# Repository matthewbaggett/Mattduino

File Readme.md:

# Mattduino Arduino Mega clone

## Why? 
Because I wanted to convert the minimal circuit of an Arduino Mega into a Eaglecad Design Block. And now that I've done that, I should make it into a schematic with all the pins broken out and aligned just like a real Arduino Mega.

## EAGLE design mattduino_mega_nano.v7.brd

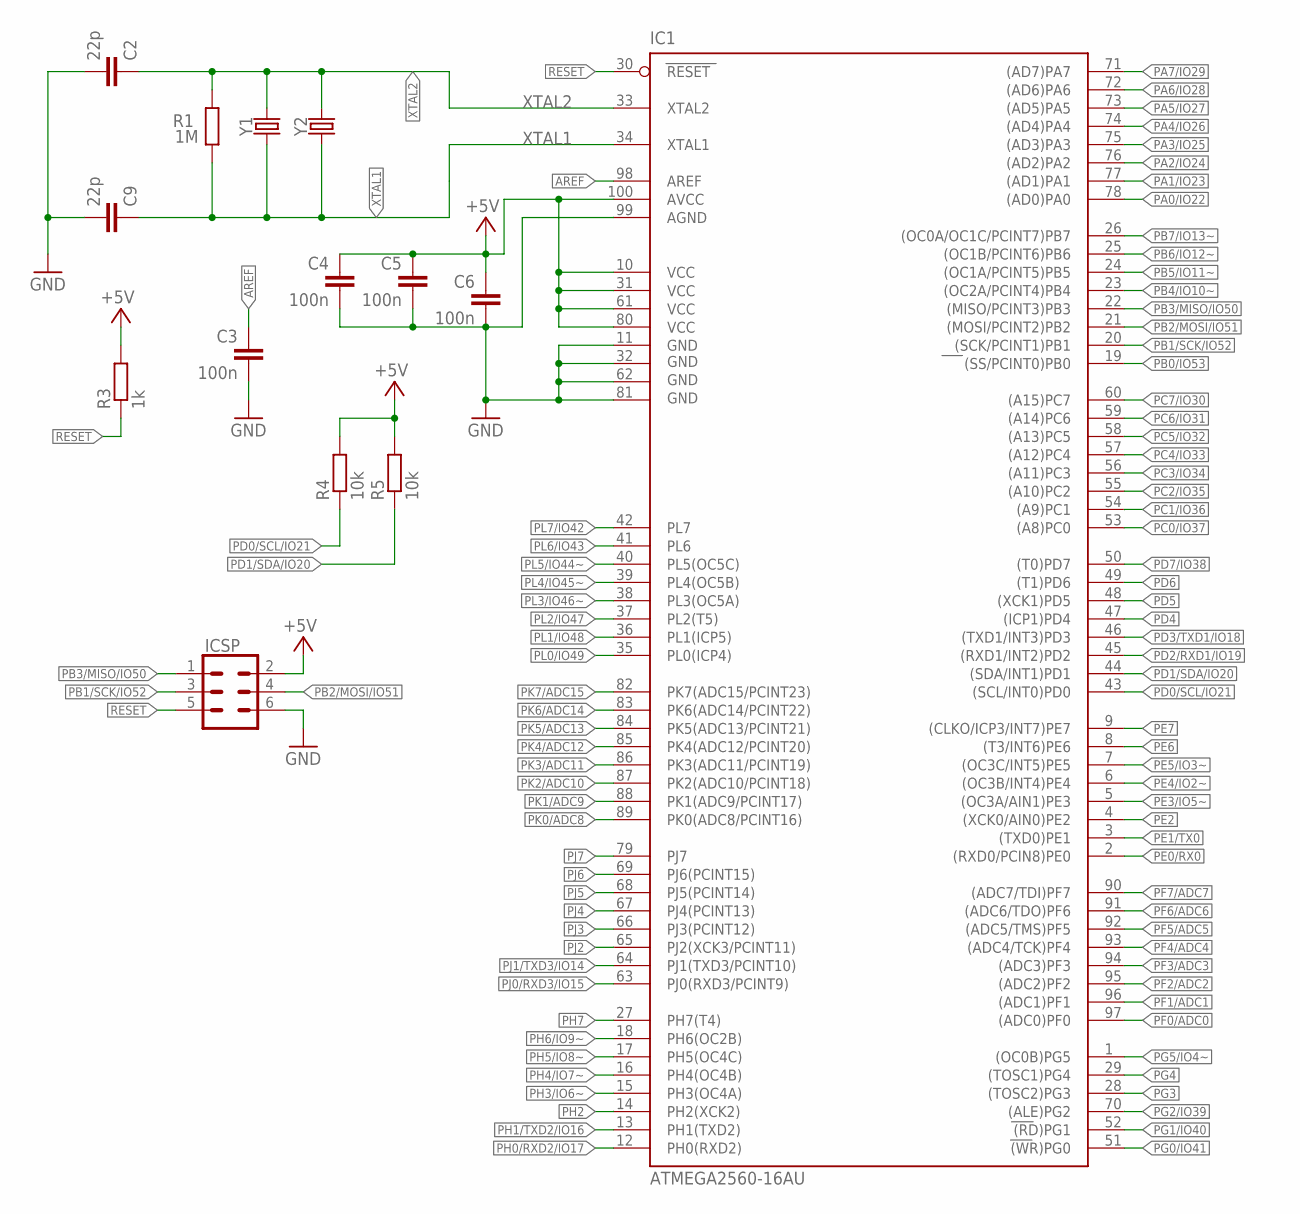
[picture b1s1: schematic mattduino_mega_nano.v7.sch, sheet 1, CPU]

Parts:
C2, C9: 22p; C0603
C3, C4, C5, C6: 100n; C0603
IC1: ATMEGA2560-16AU; TQFP100
ICSP: CONN_03X2SHROUD; 2X3-SHROUDED
R1: 1M; R0603
R3: 1k; R0603
R4, R5: 10k; R0603
Y1: CRYSTALPTH-HC49UV; HC49U
Y2: CRYSTALSMD-HC49UP; HC49UP

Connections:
+5V: C4.1, C5.1, C6.1, IC1.10 (VCC), IC1.31 (VCC1), IC1.61 (VCC2), IC1.80 (VCC3), IC1.100 (AVCC), ICSP.2, R3.2, R4.2, R5.2; also elsewhere on the board
AREF: C3.1, IC1.98 (AREF)
GND: C2.2, C3.2, C4.2, C5.2, C6.2, C9.2, IC1.11 (GND), IC1.32 (GND1), IC1.62 (GND2), IC1.81 (GND3), IC1.99 (AGND), ICSP.6; also elsewhere on the board
PA0/IO22: IC1.78 ((AD0)PA0); also elsewhere on the board
PA1/IO23: IC1.77 ((AD1)PA1); also elsewhere on the board
PA2/IO24: IC1.76 ((AD2)PA2); also elsewhere on the board
PA3/IO25: IC1.75 ((AD3)PA3); also elsewhere on the board
PA4/IO26: IC1.74 ((AD4)PA4); also elsewhere on the board
PA5/IO27: IC1.73 ((AD5)PA5); also elsewhere on the board
PA6/IO28: IC1.72 ((AD6)PA6); also elsewhere on the board
PA7/IO29: IC1.71 ((AD7)PA7); also elsewhere on the board
PB0/IO53: IC1.19 ((SS/PCINT0)PB0); also elsewhere on the board
PB1/SCK/IO52: IC1.20 ((SCK/PCINT1)PB1), ICSP.3; also elsewhere on the board
PB2/MOSI/IO51: IC1.21 ((MOSI/PCINT2)PB2), ICSP.4; also elsewhere on the board
PB3/MISO/IO50: IC1.22 ((MISO/PCINT3)PB3), ICSP.1; also elsewhere on the board
PB4/IO10~: IC1.23 ((OC2A/PCINT4)PB4); also elsewhere on the board
PB5/IO11~: IC1.24 ((OC1A/PCINT5)PB5); also elsewhere on the board
PB6/IO12~: IC1.25 ((OC1B/PCINT6)PB6); also elsewhere on the board
PB7/IO13~: IC1.26 ((OC0A/OC1C/PCINT7)PB7); also elsewhere on the board
PC0/IO37: IC1.53 ((A8)PC0); also elsewhere on the board
PC1/IO36: IC1.54 ((A9)PC1); also elsewhere on the board
PC2/IO35: IC1.55 ((A10)PC2); also elsewhere on the board
PC3/IO34: IC1.56 ((A11)PC3); also elsewhere on the board
PC4/IO33: IC1.57 ((A12)PC4); also elsewhere on the board
PC5/IO32: IC1.58 ((A13)PC5); also elsewhere on the board
PC6/IO31: IC1.59 ((A14)PC6); also elsewhere on the board
PC7/IO30: IC1.60 ((A15)PC7); also elsewhere on the board
PD0/SCL/IO21: IC1.43 ((SCL/INT0)PD0), R4.1; also elsewhere on the board
PD1/SDA/IO20: IC1.44 ((SDA/INT1)PD1), R5.1; also elsewhere on the board
PD2/RXD1/IO19: IC1.45 ((RXD1/INT2)PD2); also elsewhere on the board
PD3/TXD1/IO18: IC1.46 ((TXD1/INT3)PD3); also elsewhere on the board
PD4: IC1.47 ((ICP1)PD4)
PD5: IC1.48 ((XCK1)PD5)
PD6: IC1.49 ((T1)PD6)
PD7/IO38: IC1.50 ((T0)PD7); also elsewhere on the board
PE0/RX0: IC1.2 ((RXD0/PCIN8)PE0); also elsewhere on the board
PE1/TX0: IC1.3 ((TXD0)PE1); also elsewhere on the board
PE2: IC1.4 ((XCK0/AIN0)PE2)
PE3/IO5~: IC1.5 ((OC3A/AIN1)PE3); also elsewhere on the board
PE4/IO2~: IC1.6 ((OC3B/INT4)PE4); also elsewhere on the board
PE5/IO3~: IC1.7 ((OC3C/INT5)PE5); also elsewhere on the board
PE6: IC1.8 ((T3/INT6)PE6); also elsewhere on the board
PE7: IC1.9 ((CLKO/ICP3/INT7)PE7); also elsewhere on the board
PF0/ADC0: IC1.97 ((ADC0)PF0); also elsewhere on the board
PF1/ADC1: IC1.96 ((ADC1)PF1); also elsewhere on the board
PF2/ADC2: IC1.95 ((ADC2)PF2); also elsewhere on the board
PF3/ADC3: IC1.94 ((ADC3)PF3); also elsewhere on the board
PF4/ADC4: IC1.93 ((ADC4/TCK)PF4); also elsewhere on the board
PF5/ADC5: IC1.92 ((ADC5/TMS)PF5); also elsewhere on the board
PF6/ADC6: IC1.91 ((ADC6/TDO)PF6); also elsewhere on the board
PF7/ADC7: IC1.90 ((ADC7/TDI)PF7); also elsewhere on the board
PG0/IO41: IC1.51 ((WR)PG0); also elsewhere on the board
PG1/IO40: IC1.52 ((RD)PG1); also elsewhere on the board
PG2/IO39: IC1.70 ((ALE)PG2); also elsewhere on the board
PG3: IC1.28 ((TOSC2)PG3)
PG4: IC1.29 ((TOSC1)PG4)
PG5/IO4~: IC1.1 ((OC0B)PG5); also elsewhere on the board
PH0/RXD2/IO17: IC1.12 (PH0(RXD2)); also elsewhere on the board
PH1/TXD2/IO16: IC1.13 (PH1(TXD2)); also elsewhere on the board
PH2: IC1.14 (PH2(XCK2)); also elsewhere on the board
PH3/IO6~: IC1.15 (PH3(OC4A)); also elsewhere on the board
PH4/IO7~: IC1.16 (PH4(OC4B)); also elsewhere on the board
PH5/IO8~: IC1.17 (PH5(OC4C)); also elsewhere on the board
PH6/IO9~: IC1.18 (PH6(OC2B)); also elsewhere on the board
PH7: IC1.27 (PH7(T4))
PJ0/RXD3/IO15: IC1.63 (PJ0(RXD3/PCINT9)); also elsewhere on the board
PJ1/TXD3/IO14: IC1.64 (PJ1(TXD3/PCINT10)); also elsewhere on the board
PJ2: IC1.65 (PJ2(XCK3/PCINT11))
PJ3: IC1.66 (PJ3(PCINT12))
PJ4: IC1.67 (PJ4(PCINT13))
PJ5: IC1.68 (PJ5(PCINT14))
PJ6: IC1.69 (PJ6(PCINT15))
PJ7: IC1.79 (PJ7)
PK0/ADC8: IC1.89 (PK0(ADC8/PCINT16)); also elsewhere on the board
PK1/ADC9: IC1.88 (PK1(ADC9/PCINT17)); also elsewhere on the board
PK2/ADC10: IC1.87 (PK2(ADC10/PCINT18)); also elsewhere on the board
PK3/ADC11: IC1.86 (PK3(ADC11/PCINT19)); also elsewhere on the board
PK4/ADC12: IC1.85 (PK4(ADC12/PCINT20)); also elsewhere on the board
PK5/ADC13: IC1.84 (PK5(ADC13/PCINT21)); also elsewhere on the board
PK6/ADC14: IC1.83 (PK6(ADC14/PCINT22)); also elsewhere on the board
PK7/ADC15: IC1.82 (PK7(ADC15/PCINT23)); also elsewhere on the board
PL0/IO49: IC1.35 (PL0(ICP4)); also elsewhere on the board
PL1/IO48: IC1.36 (PL1(ICP5)); also elsewhere on the board
PL2/IO47: IC1.37 (PL2(T5)); also elsewhere on the board
PL3/IO46~: IC1.38 (PL3(OC5A)); also elsewhere on the board
PL4/IO45~: IC1.39 (PL4(OC5B)); also elsewhere on the board
PL5/IO44~: IC1.40 (PL5(OC5C)); also elsewhere on the board
PL6/IO43: IC1.41 (PL6); also elsewhere on the board
PL7/IO42: IC1.42 (PL7); also elsewhere on the board
RESET: IC1.30 (RESET), ICSP.5, R3.1; also elsewhere on the board
XTAL1: C9.1, IC1.34 (XTAL1), R1.1, Y1.1, Y2.1
XTAL2: C2.1, IC1.33 (XTAL2), R1.2, Y1.2, Y2.2

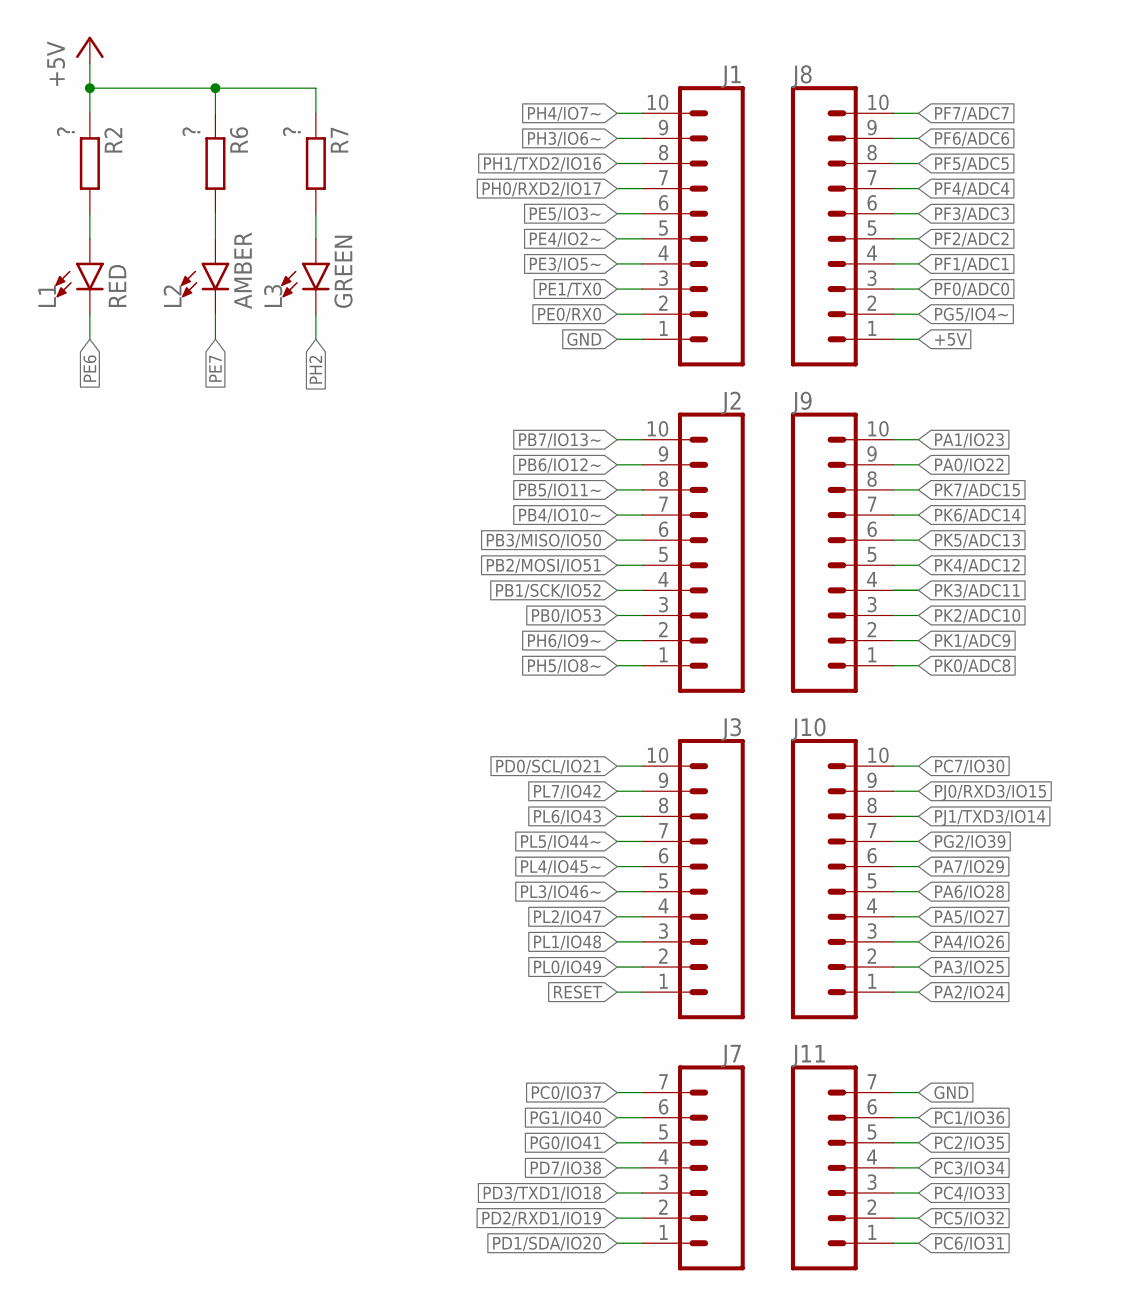
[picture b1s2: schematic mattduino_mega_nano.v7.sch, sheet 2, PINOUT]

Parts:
J1, J2, J3, J8, J9, J10: CONN_10LOCK; 1X10_LOCK
J7, J11: CONN_07LOCK; 1X07_LOCK
L1: RED; LED-0603
L2: AMBER; LED-0603
L3: GREEN; LED-0603
R2, R6, R7: ?; R0603

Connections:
+5V: J8.1, R2.1, R6.1, R7.1; also elsewhere on the board
GND: J1.1, J11.7; also elsewhere on the board
unnamed: L1.A, R2.2
unnamed: L2.A, R6.2
unnamed: L3.A, R7.2
PA0/IO22: J9.9; also elsewhere on the board
PA1/IO23: J9.10; also elsewhere on the board
PA2/IO24: J10.1; also elsewhere on the board
PA3/IO25: J10.2; also elsewhere on the board
PA4/IO26: J10.3; also elsewhere on the board
PA5/IO27: J10.4; also elsewhere on the board
PA6/IO28: J10.5; also elsewhere on the board
PA7/IO29: J10.6; also elsewhere on the board
PB0/IO53: J2.3; also elsewhere on the board
PB1/SCK/IO52: J2.4; also elsewhere on the board
PB2/MOSI/IO51: J2.5; also elsewhere on the board
PB3/MISO/IO50: J2.6; also elsewhere on the board
PB4/IO10~: J2.7; also elsewhere on the board
PB5/IO11~: J2.8; also elsewhere on the board
PB6/IO12~: J2.9; also elsewhere on the board
PB7/IO13~: J2.10; also elsewhere on the board
PC0/IO37: J7.7; also elsewhere on the board
PC1/IO36: J11.6; also elsewhere on the board
PC2/IO35: J11.5; also elsewhere on the board
PC3/IO34: J11.4; also elsewhere on the board
PC4/IO33: J11.3; also elsewhere on the board
PC5/IO32: J11.2; also elsewhere on the board
PC6/IO31: J11.1; also elsewhere on the board
PC7/IO30: J10.10; also elsewhere on the board
PD0/SCL/IO21: J3.10; also elsewhere on the board
PD1/SDA/IO20: J7.1; also elsewhere on the board
PD2/RXD1/IO19: J7.2; also elsewhere on the board
PD3/TXD1/IO18: J7.3; also elsewhere on the board
PD7/IO38: J7.4; also elsewhere on the board
PE0/RX0: J1.2; also elsewhere on the board
PE1/TX0: J1.3; also elsewhere on the board
PE3/IO5~: J1.4; also elsewhere on the board
PE4/IO2~: J1.5; also elsewhere on the board
PE5/IO3~: J1.6; also elsewhere on the board
PE6: L1.C; also elsewhere on the board
PE7: L2.C; also elsewhere on the board
PF0/ADC0: J8.3; also elsewhere on the board
PF1/ADC1: J8.4; also elsewhere on the board
PF2/ADC2: J8.5; also elsewhere on the board
PF3/ADC3: J8.6; also elsewhere on the board
PF4/ADC4: J8.7; also elsewhere on the board
PF5/ADC5: J8.8; also elsewhere on the board
PF6/ADC6: J8.9; also elsewhere on the board
PF7/ADC7: J8.10; also elsewhere on the board
PG0/IO41: J7.5; also elsewhere on the board
PG1/IO40: J7.6; also elsewhere on the board
PG2/IO39: J10.7; also elsewhere on the board
PG5/IO4~: J8.2; also elsewhere on the board
PH0/RXD2/IO17: J1.7; also elsewhere on the board
PH1/TXD2/IO16: J1.8; also elsewhere on the board
PH2: L3.C; also elsewhere on the board
PH3/IO6~: J1.9; also elsewhere on the board
PH4/IO7~: J1.10; also elsewhere on the board
PH5/IO8~: J2.1; also elsewhere on the board
PH6/IO9~: J2.2; also elsewhere on the board
PJ0/RXD3/IO15: J10.9; also elsewhere on the board
PJ1/TXD3/IO14: J10.8; also elsewhere on the board
PK0/ADC8: J9.1; also elsewhere on the board
PK1/ADC9: J9.2; also elsewhere on the board
PK2/ADC10: J9.3; also elsewhere on the board
PK3/ADC11: J9.4; also elsewhere on the board
PK4/ADC12: J9.5; also elsewhere on the board
PK5/ADC13: J9.6; also elsewhere on the board
PK6/ADC14: J9.7; also elsewhere on the board
PK7/ADC15: J9.8; also elsewhere on the board
PL0/IO49: J3.2; also elsewhere on the board
PL1/IO48: J3.3; also elsewhere on the board
PL2/IO47: J3.4; also elsewhere on the board
PL3/IO46~: J3.5; also elsewhere on the board
PL4/IO45~: J3.6; also elsewhere on the board
PL5/IO44~: J3.7; also elsewhere on the board
PL6/IO43: J3.8; also elsewhere on the board
PL7/IO42: J3.9; also elsewhere on the board
RESET: J3.1; also elsewhere on the board

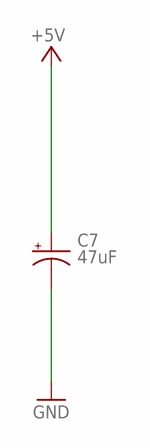
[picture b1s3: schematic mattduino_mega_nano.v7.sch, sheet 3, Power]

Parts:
C7: 47uF; PANASONIC_D

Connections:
+5V: C7.+; also elsewhere on the board
GND: C7.-; also elsewhere on the board

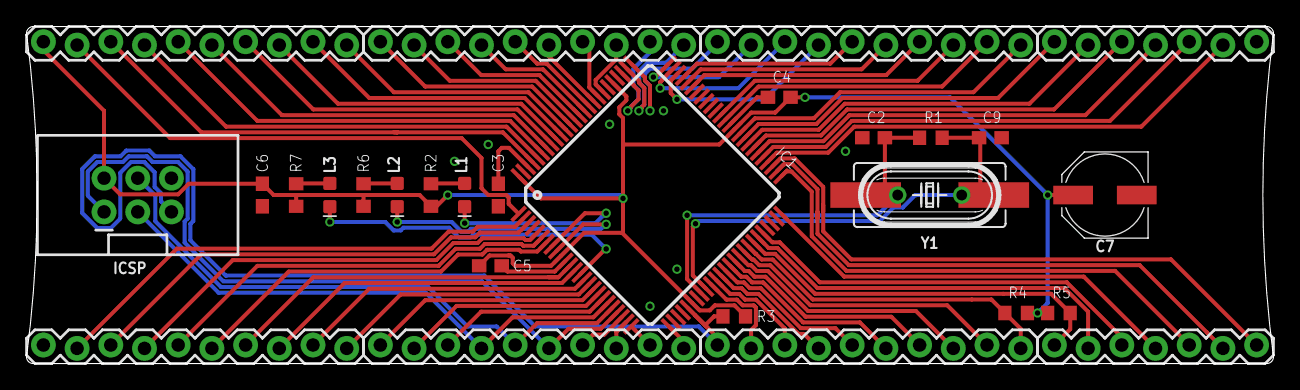
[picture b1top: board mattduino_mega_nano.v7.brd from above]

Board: 2 copper layers, 94.0 x 25.4 mm, 29 parts (0 on the bottom side), 82 nets.

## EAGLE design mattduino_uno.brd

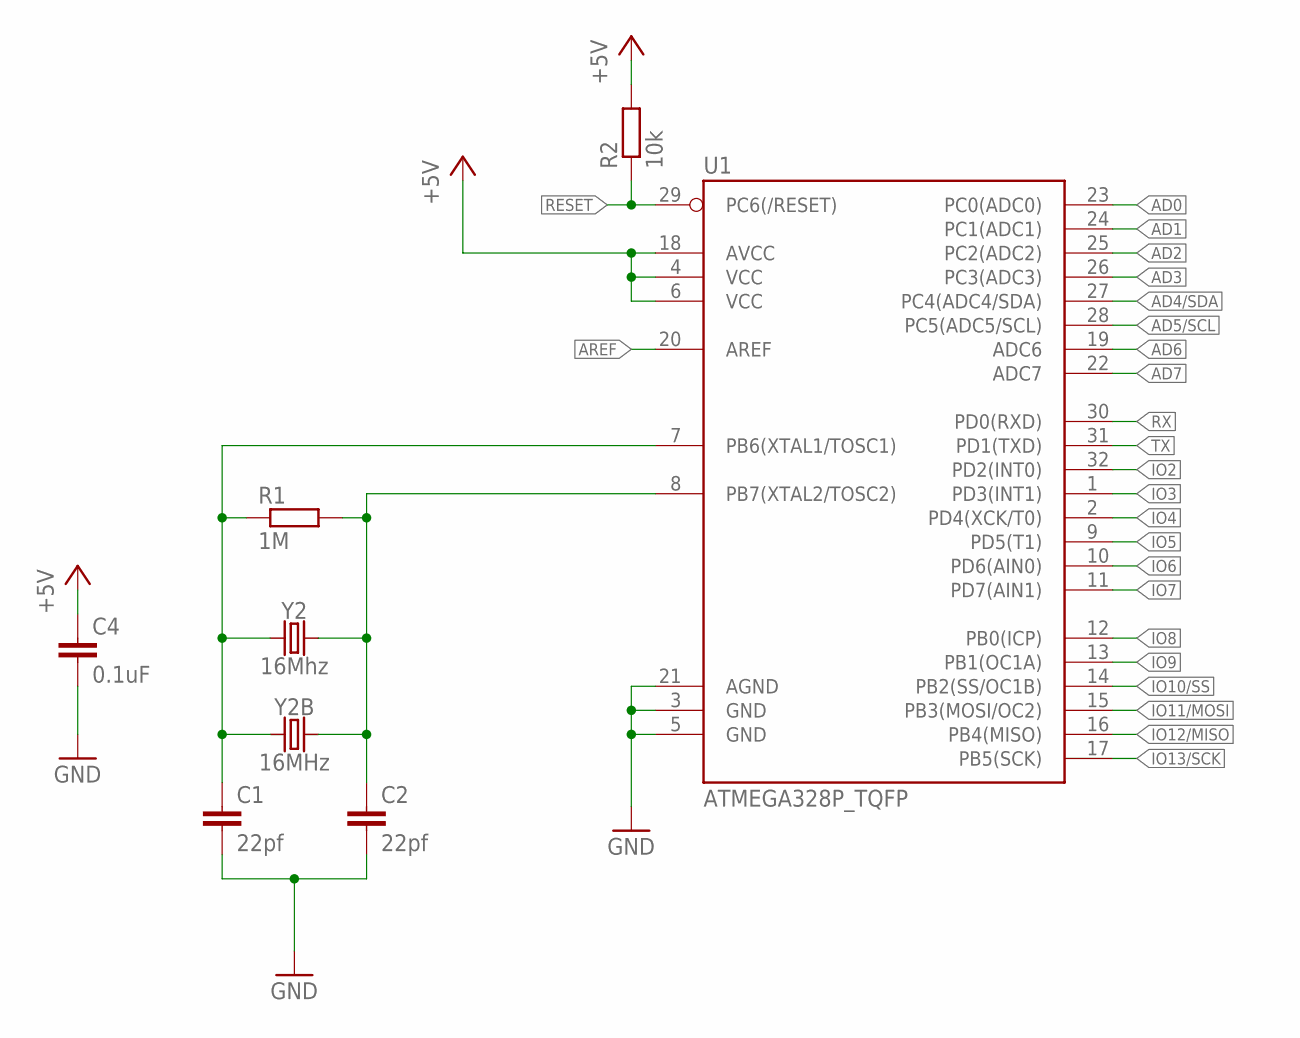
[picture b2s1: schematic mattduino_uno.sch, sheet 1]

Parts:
C1, C2: 22pf; C0603
C4: 0.1uF; C0603
R1: 1M; R0603
R2: 10k; R0603
U1: ATMEGA328P_TQFP; TQFP32-08
Y2: 16Mhz; HC49UP
Y2B: 16MHz; HC49U

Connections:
328_OSC1: C1.1, R1.1, U1.7 (PB6(XTAL1/TOSC1)), Y2.1, Y2B.1
328_OSC2: C2.1, R1.2, U1.8 (PB7(XTAL2/TOSC2)), Y2.2, Y2B.2
+5V: C4.1, R2.2, U1.4 (VCC), U1.6 (VCC), U1.18 (AVCC); also elsewhere on the board
AD0: U1.23 (PC0(ADC0)); also elsewhere on the board
AD1: U1.24 (PC1(ADC1)); also elsewhere on the board
AD2: U1.25 (PC2(ADC2)); also elsewhere on the board
AD3: U1.26 (PC3(ADC3)); also elsewhere on the board
AD4/SDA: U1.27 (PC4(ADC4/SDA)); also elsewhere on the board
AD5/SCL: U1.28 (PC5(ADC5/SCL)); also elsewhere on the board
AD6: U1.19 (ADC6); also elsewhere on the board
AD7: U1.22 (ADC7); also elsewhere on the board
AREF: U1.20 (AREF); also elsewhere on the board
GND: C1.2, C2.2, C4.2, U1.3 (GND), U1.5 (GND), U1.21 (AGND); also elsewhere on the board
IO2: U1.32 (PD2(INT0)); also elsewhere on the board
IO3: U1.1 (PD3(INT1)); also elsewhere on the board
IO4: U1.2 (PD4(XCK/T0)); also elsewhere on the board
IO5: U1.9 (PD5(T1)); also elsewhere on the board
IO6: U1.10 (PD6(AIN0)); also elsewhere on the board
IO7: U1.11 (PD7(AIN1)); also elsewhere on the board
IO8: U1.12 (PB0(ICP)); also elsewhere on the board
IO9: U1.13 (PB1(OC1A)); also elsewhere on the board
IO10/SS: U1.14 (PB2(SS/OC1B)); also elsewhere on the board
IO11/MOSI: U1.15 (PB3(MOSI/OC2)); also elsewhere on the board
IO12/MISO: U1.16 (PB4(MISO)); also elsewhere on the board
IO13/SCK: U1.17 (PB5(SCK)); also elsewhere on the board
RESET: R2.1, U1.29 (PC6(/RESET)); also elsewhere on the board
RX: U1.30 (PD0(RXD)); also elsewhere on the board
TX: U1.31 (PD1(TXD)); also elsewhere on the board

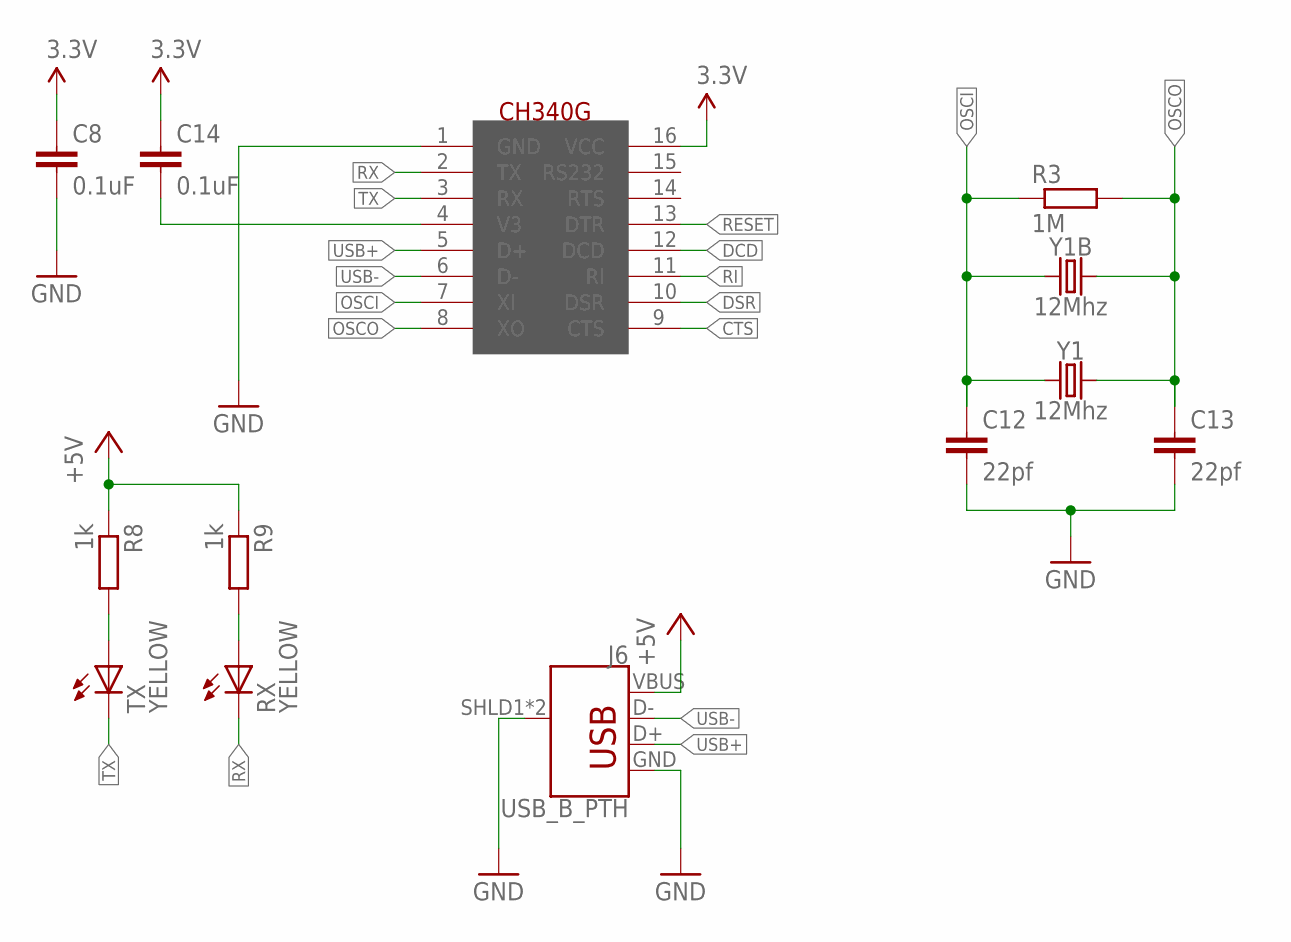
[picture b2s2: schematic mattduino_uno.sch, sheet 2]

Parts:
C8, C14: 0.1uF; C0603
C12, C13: 22pf; C0603
IC3: CH340G; SOIC16
J6: USB_B_PTH; USB-B-PTH
R3: 1M; R0603
R8, R9: 1k; R0603
RX: YELLOW; CHIP-LED0603
TX: YELLOW; CHIP-LED0603
Y1: 12Mhz; HC49U
Y1B: 12Mhz; HC49UP

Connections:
3.3V: C8.1, C14.1, IC3.16 (VCC); also elsewhere on the board
+5V: J6.VBUS, R8.1, R9.1; also elsewhere on the board
CTS: IC3.9 (CTS)
DCD: IC3.12 (DCD)
DSR: IC3.10 (DSR)
GND: C8.2, C12.2, C13.2, IC3.1 (GND), J6.GND, J6.SHLD1 (SHIELD), J6.SHLD2 (SHIELD); also elsewhere on the board
unnamed: R8.2, TX.A
unnamed: R9.2, RX.A
OSCI: C12.1, IC3.7 (XI), R3.1, Y1.1, Y1B.1
OSCO: C13.1, IC3.8 (XO), R3.2, Y1.2, Y1B.2
RESET: IC3.13 (DTR); also elsewhere on the board
RI: IC3.11 (RI)
RX: IC3.2 (TX), RX.C; also elsewhere on the board
TX: IC3.3 (RX), TX.C; also elsewhere on the board
USB+: IC3.5 (D+), J6.D+
USB-: IC3.6 (D-), J6.D-
V3: C14.2, IC3.4 (V3)

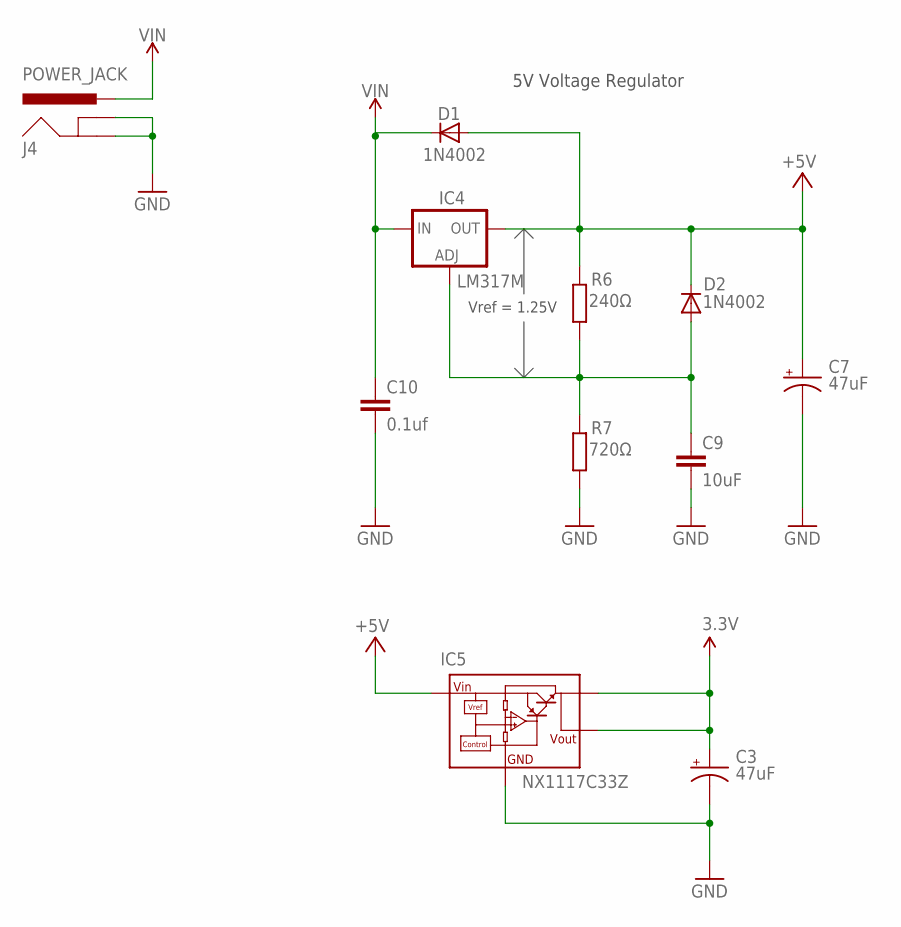
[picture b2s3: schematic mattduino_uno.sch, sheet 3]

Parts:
C3, C7: 47uF; PANASONIC_D
C9: 10uF; C0603
C10: 0.1uf; C0603
D1, D2: 1N4002; SOD-123
IC4: LM317MBSTT3; SOT223; PARTNUMBER LM317M
IC5: NX1117C33Z; SOT223
J4: POWER_JACK; POWER_JACK_PTH
R6: 240Ω; R0603
R7: 720Ω; R0603

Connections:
3.3V: C3.+, IC5.2 (VOUT1), IC5.4 (VOUT); also elsewhere on the board
+5V: C7.+, D1.A, D2.C, IC4.4 (OUT), IC5.3 (VIN), R6.2; also elsewhere on the board
GND: C3.-, C7.-, C9.2, C10.2, IC5.1 (GND), J4.GND, J4.GNDBREAK, R7.1; also elsewhere on the board
unnamed: C9.1, D2.A, IC4.1 (ADJ), R6.1, R7.2
VIN: C10.1, D1.C, IC4.3 (IN), J4.PWR; also elsewhere on the board

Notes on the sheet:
5V Voltage Regulator
Vref = 1.25V

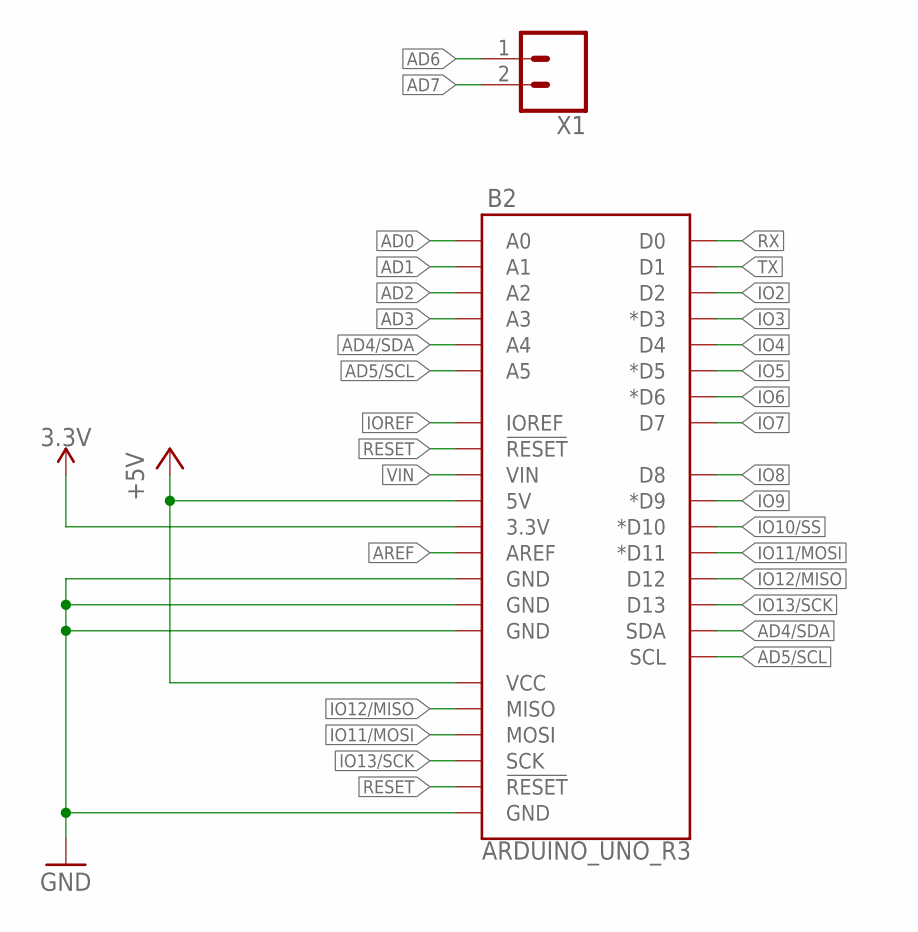
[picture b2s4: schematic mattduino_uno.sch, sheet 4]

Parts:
B2: ARDUINO_UNO_R3; ARDUINO_R3
X1: CONN_02; 1X02

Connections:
3.3V: B2.3.3V; also elsewhere on the board
+5V: B2.5V, B2.VCC; also elsewhere on the board
AD0: B2.A0; also elsewhere on the board
AD1: B2.A1; also elsewhere on the board
AD2: B2.A2; also elsewhere on the board
AD3: B2.A3; also elsewhere on the board
AD4/SDA: B2.A4, B2.SDA; also elsewhere on the board
AD5/SCL: B2.A5, B2.SCL; also elsewhere on the board
AD6: X1.1; also elsewhere on the board
AD7: X1.2; also elsewhere on the board
AREF: B2.AREF; also elsewhere on the board
GND: B2.GND@1 (GND), B2.GND@2 (GND), B2.GND@3 (GND), B2.GND@4 (GND); also elsewhere on the board
IO2: B2.D2; also elsewhere on the board
IO3: B2.D3 (*D3); also elsewhere on the board
IO4: B2.D4; also elsewhere on the board
IO5: B2.D5 (*D5); also elsewhere on the board
IO6: B2.D6 (*D6); also elsewhere on the board
IO7: B2.D7; also elsewhere on the board
IO8: B2.D8; also elsewhere on the board
IO9: B2.D9 (*D9); also elsewhere on the board
IO10/SS: B2.D10 (*D10); also elsewhere on the board
IO11/MOSI: B2.D11 (*D11), B2.MOSI; also elsewhere on the board
IO12/MISO: B2.D12, B2.MISO; also elsewhere on the board
IO13/SCK: B2.D13, B2.SCK; also elsewhere on the board
IOREF: B2.IOREF
RESET: B2.RESET@1 (!RESET!), B2.RESET@2 (!RESET!); also elsewhere on the board
RX: B2.D0; also elsewhere on the board
TX: B2.D1; also elsewhere on the board
VIN: B2.VIN; also elsewhere on the board

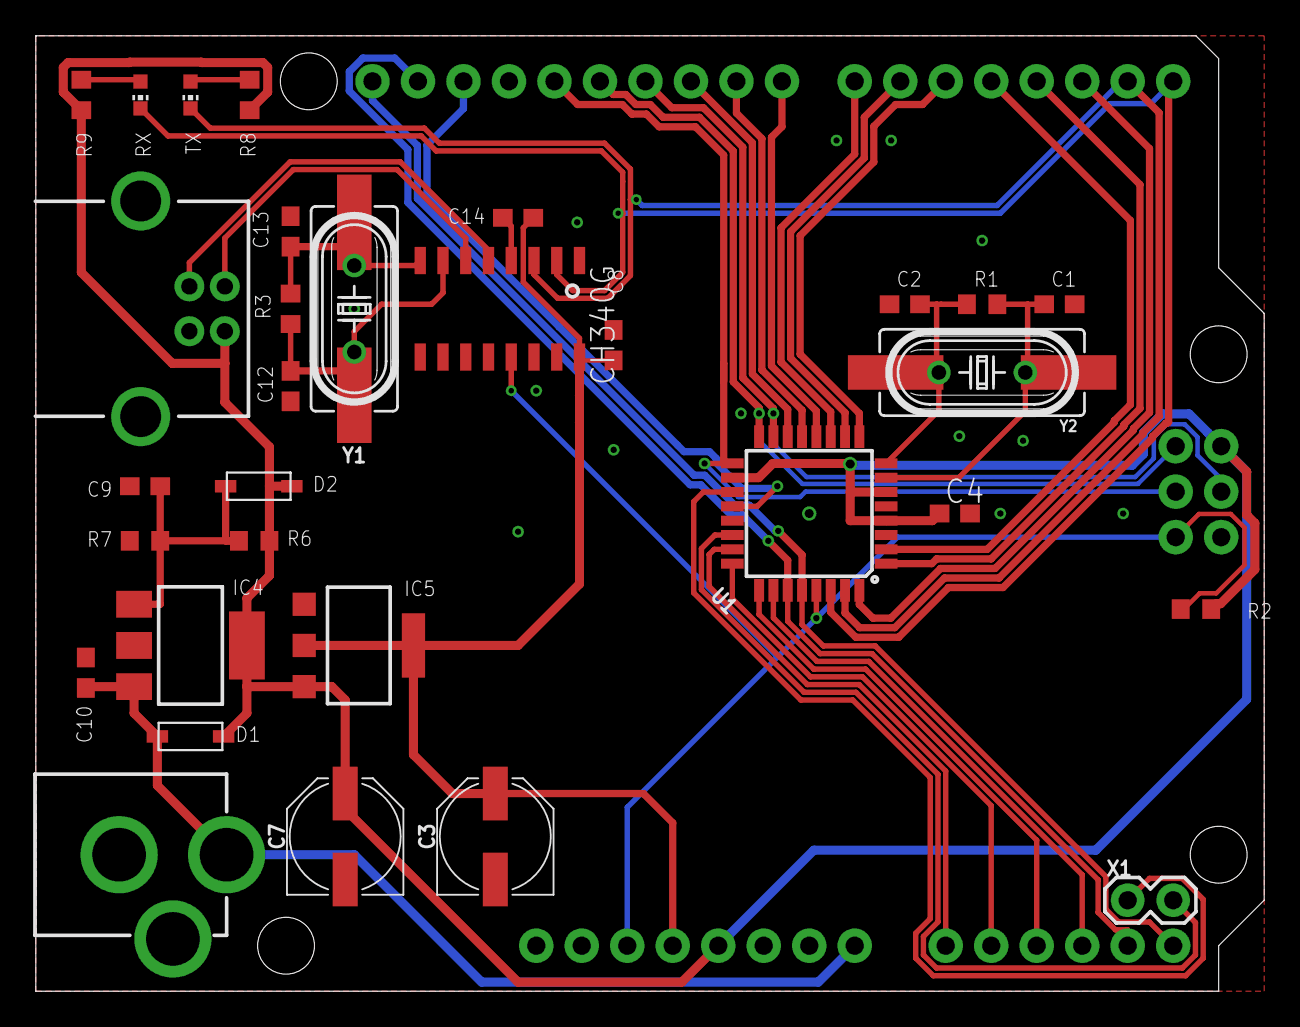
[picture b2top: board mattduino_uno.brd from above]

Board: 2 copper layers, 68.6 x 53.3 mm, 34 parts (0 on the bottom side), 38 nets.

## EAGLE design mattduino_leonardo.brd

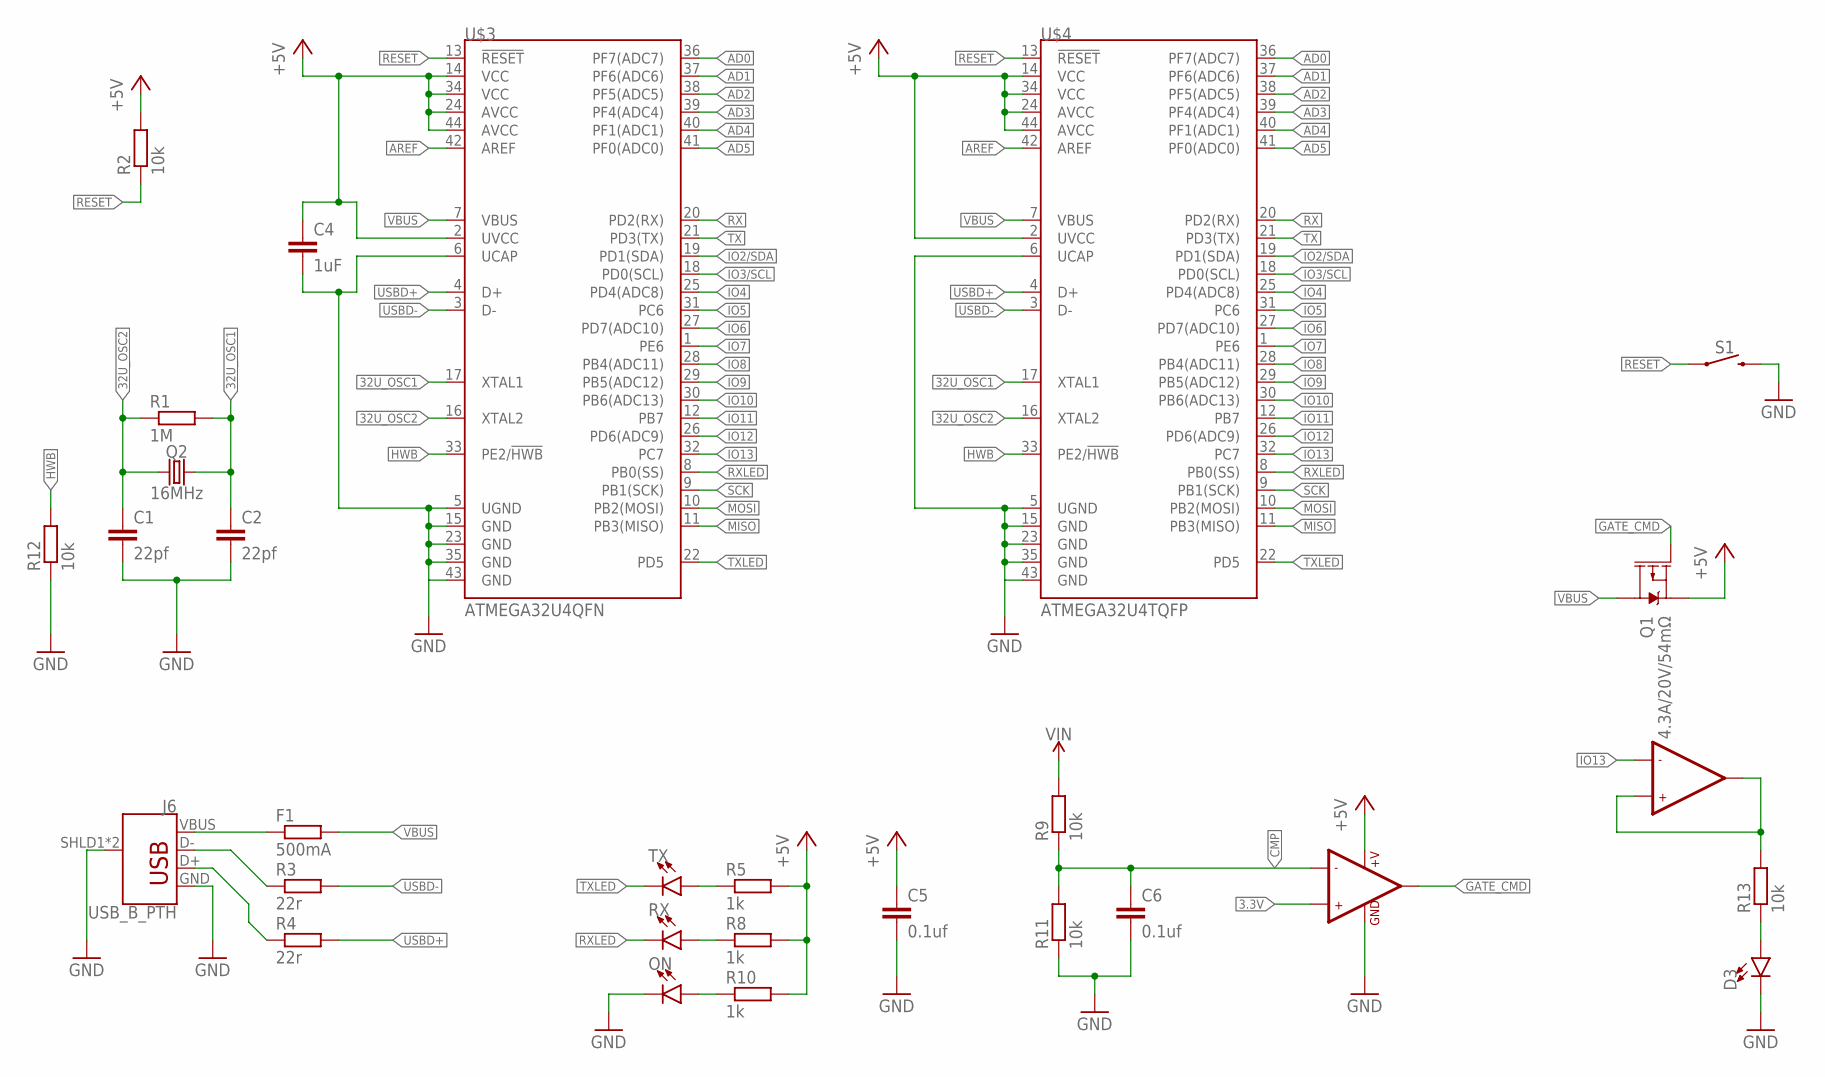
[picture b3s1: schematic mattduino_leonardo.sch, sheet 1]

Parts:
C1, C2: 22pf; C1206
C4: 1uF; C1206
C5, C6: 0.1uf; C1206
D3: LED1206; LED-1206
F1: 500mA; R1206
J6: USB_B_PTH; USB-B-PTH
ON: LED1206; LED-1206
Q1: 4.3A/20V/54mΩ; SOT23-3
Q2: 16MHz; HC49UP
R1: 1M; R1206
R2, R9, R11, R12, R13: 10k; R1206
R3, R4: 22r; R1206
R5, R8, R10: 1k; R1206
RX: LED1206; LED-1206
S1: MOMENTARY-SWITCH-SPST-PTH-6.0MM-KIT; TACTILE_SWITCH_PTH_6.0MM_KIT
TX: LED1206; LED-1206
U$1: LMV358; SO08
U$3: ATMEGA32U4QFN; SPARKFUN-DIGITALIC_QFN-44
U$4: ATMEGA32U4TQFP; SPARKFUN-DIGITALIC_TQFP44

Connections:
3.3V: U$1.3 (+IN1); also elsewhere on the board
32U_OSC1: C2.1, Q2.2, R1.2, U$3.17 (XTAL1), U$4.17 (XTAL1)
32U_OSC2: C1.1, Q2.1, R1.1, U$3.16 (XTAL2), U$4.16 (XTAL2)
+5V: C4.1, C5.1, Q1.2 (S), R2.2, R5.2, R8.2, R10.2, U$1.8 (+V), U$3.2 (UVCC), U$3.14 (VCC), U$3.24 (AVCC), U$3.34 (VCC), U$3.44 (AVCC), U$4.2 (UVCC), U$4.14 (VCC), U$4.24 (AVCC), U$4.34 (VCC), U$4.44 (AVCC); also elsewhere on the board
AD0: U$3.36 (PF7(ADC7)), U$4.36 (PF7(ADC7)); also elsewhere on the board
AD1: U$3.37 (PF6(ADC6)), U$4.37 (PF6(ADC6)); also elsewhere on the board
AD2: U$3.38 (PF5(ADC5)), U$4.38 (PF5(ADC5)); also elsewhere on the board
AD3: U$3.39 (PF4(ADC4)), U$4.39 (PF4(ADC4)); also elsewhere on the board
AD4: U$3.40 (PF1(ADC1)), U$4.40 (PF1(ADC1)); also elsewhere on the board
AD5: U$3.41 (PF0(ADC0)), U$4.41 (PF0(ADC0)); also elsewhere on the board
AREF: U$3.42 (AREF), U$4.42 (AREF); also elsewhere on the board
CMP: C6.1, R9.1, R11.2, U$1.2 (-IN1)
GATE_CMD: Q1.1 (G), U$1.1 (OUT1)
GND: C1.2, C2.2, C4.2, C5.2, C6.2, D3.C, J6.GND, J6.SHLD1 (SHIELD), J6.SHLD2 (SHIELD), ON.C, R11.1, R12.1, S1.3 (2), U$1.4 (GND), U$3.5 (UGND), U$3.6 (UCAP), U$3.15 (GND), U$3.23 (GND), U$3.35 (GND), U$3.43 (GND), U$4.5 (UGND), U$4.6 (UCAP), U$4.15 (GND), U$4.23 (GND), U$4.35 (GND), U$4.43 (GND); also elsewhere on the board
HWB: R12.2, U$3.33 (PE2/!HWB), U$4.33 (PE2/!HWB)
IO2/SDA: U$3.19 (PD1(SDA)), U$4.19 (PD1(SDA)); also elsewhere on the board
IO3/SCL: U$3.18 (PD0(SCL)), U$4.18 (PD0(SCL)); also elsewhere on the board
IO4: U$3.25 (PD4(ADC8)), U$4.25 (PD4(ADC8)); also elsewhere on the board
IO5: U$3.31 (PC6), U$4.31 (PC6); also elsewhere on the board
IO6: U$3.27 (PD7(ADC10)), U$4.27 (PD7(ADC10)); also elsewhere on the board
IO7: U$3.1 (PE6), U$4.1 (PE6); also elsewhere on the board
IO8: U$3.28 (PB4(ADC11)), U$4.28 (PB4(ADC11)); also elsewhere on the board
IO9: U$3.29 (PB5(ADC12)), U$4.29 (PB5(ADC12)); also elsewhere on the board
IO10: U$3.30 (PB6(ADC13)), U$4.30 (PB6(ADC13)); also elsewhere on the board
IO11: U$3.12 (PB7), U$4.12 (PB7); also elsewhere on the board
IO12: U$3.26 (PD6(ADC9)), U$4.26 (PD6(ADC9)); also elsewhere on the board
IO13: U$1.6 (-IN2), U$3.32 (PC7), U$4.32 (PC7); also elsewhere on the board
MISO: U$3.11 (PB3(MISO)), U$4.11 (PB3(MISO)); also elsewhere on the board
MOSI: U$3.10 (PB2(MOSI)), U$4.10 (PB2(MOSI)); also elsewhere on the board
unnamed: R13.2, U$1.5 (+IN2), U$1.7 (OUT2)
unnamed: ON.A, R10.1
unnamed: D3.A, R13.1
unnamed: R8.1, RX.A
unnamed: R5.1, TX.A
RESET: R2.1, S1.1, U$3.13 (!RESET), U$4.13 (!RESET); also elsewhere on the board
RX: U$3.20 (PD2(RX)), U$4.20 (PD2(RX)); also elsewhere on the board
RXLED: RX.C, U$3.8 (PB0(SS)), U$4.8 (PB0(SS))
SCK: U$3.9 (PB1(SCK)), U$4.9 (PB1(SCK)); also elsewhere on the board
TX: U$3.21 (PD3(TX)), U$4.21 (PD3(TX)); also elsewhere on the board
TXLED: TX.C, U$3.22 (PD5), U$4.22 (PD5)
USBD+: R4.2, U$3.4 (D+), U$4.4 (D+)
USBD-: R3.2, U$3.3 (D-), U$4.3 (D-)
USBR+: J6.D+, R4.1
USBR-: J6.D-, R3.1
VBUS: F1.2, Q1.3 (D), U$3.7 (VBUS), U$4.7 (VBUS)
VBUS_UNFUSED: F1.1, J6.VBUS
VIN: R9.2; also elsewhere on the board

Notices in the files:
parts and their libraries:
SparkFun-IC-Amplifiers: Licensing: Creative Commons ShareAlike 4.0 International - https://creativecommons.org/licenses/by-sa/4.0
SparkFun: Licensing: CC v3.0 Share-Alike You are welcome to use this library for commercial purposes.
